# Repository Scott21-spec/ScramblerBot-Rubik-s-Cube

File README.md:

# ScramblerBot-Rubik's-Cube-For WCA Competitions
Robot capaz de resolver o desarmar cualquier cubo de rubik 3x3 con el uso servomotores, cámara e inteligencia artificial para la detección de colores, figuras o números.

Es la mejor opción para su uso en las competencias internacionales y nacionales de cubo de rubik (WCA), debido a que sólo se coloca el cubo dentro del robot sin necesidad de modificar el cubo o utilizar un cubo especial para su reconocimiento del estado actual.

Modos de uso:
  - Modo de Desordenamiento (Scrambler mode): 
En este modo, el sistema actúa como un actuador esclavo para competencias oficiales. Recibe de forma remota una secuencia de desordenamiento (algoritmo de scramble) validada por la WCA. Tras la ejecución mecánica automatizada de los movimientos, el servidor web local genera un reporte digital en formato PDF. Este documento incluye el registro exacto de la secuencia aplicada, el algoritmo de resolución correspondiente y representaciones gráficas del estado final del cubo (planos 2D y renderizado 3D). Por normativas de seguridad y confidencialidad competitiva, el acceso a este reporte es de carácter restringido, alojándose únicamente en el entorno del servidor para la validación exclusiva de los jueces o administradores del torneo.

  - Modo de Autogeneración y Entrenamiento (Auto-Scramble & Practice Mode):
Concebida como una herramienta de entrenamiento para competidores (speedcubers), esta modalidad permite al microcontrolador generar de manera autónoma una secuencia aleatoria de desordenamiento que cumple estrictamente con los estándares y métricas de la WCA. Una vez que el robot aplica mecánicamente la secuencia generada, el sistema emite un reporte digital homólogo al de la Modalidad 1. A diferencia del modo oficial, este documento es de acceso público y descargable a través de la interfaz web, permitiendo al usuario analizar el estado del cubo, la secuencia aplicada y la solución teórica propuesta para fines de estudio y práctica.

  - Resolución Optimizada (Solve Mode):
Orientada al análisis algorítmico, esta función permite evaluar el estado físico actual de un cubo ingresado por el usuario utilizando el sistema de visión artificial integrado. A partir del mapeo de las caras, el procesador calcula la ruta de resolución más corta (optimizando la cantidad de movimientos requeridos) y procede a su ejecución mecánica. Finalmente, el sistema documenta el proceso generando un reporte descargable que detalla el estado inicial detectado, la cinemática de los movimientos aplicados y la solución óptima ejecutada.

Proyecto de la materia 'Proyecto 3' del 8vo semestre de la carrera Mecatrónica - Facultad de Ingeniería - Universidad Nacional de Asunción - San Lorenzo - Paraguay.

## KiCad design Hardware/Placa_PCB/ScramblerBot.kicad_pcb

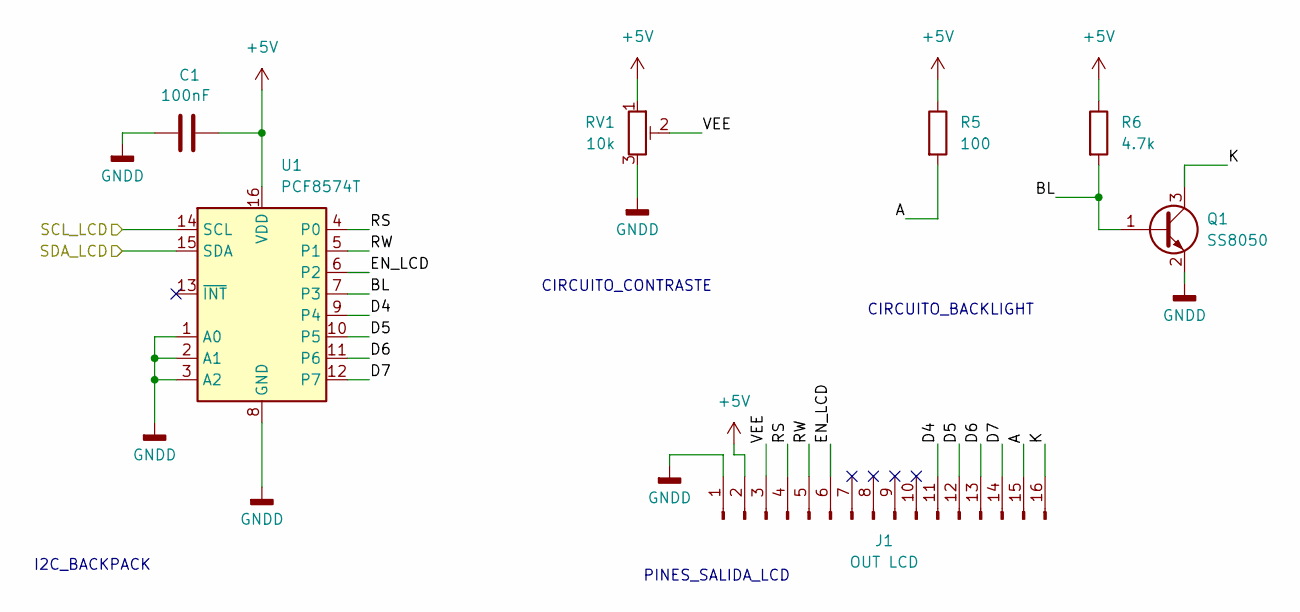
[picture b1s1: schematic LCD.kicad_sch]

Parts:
C1: 100nF; C_0805_2012Metric_Pad1.18x1.45mm_HandSolder
J1: OUT LCD; PinSocket_1x16_P2.54mm_Vertical
Q1: SS8050; SOT-23
R5: 100; R_0805_2012Metric_Pad1.20x1.40mm_HandSolder
R6: 4.7k; R_0805_2012Metric_Pad1.20x1.40mm_HandSolder
RV1: 10k; Potentiometer_Bourns_3314G_Vertical
U1: PCF8574T; SOIC-16W_7.5x10.3mm_P1.27mm

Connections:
+5V: C1.1, J1.2, R5.1, R6.1, RV1.1, U1.16 (VDD); also elsewhere on the board
/Level Shifter LCD/SCL_LCD: U1.14 (SCL); also elsewhere on the board
/Level Shifter LCD/SDA_LCD: U1.15 (SDA); also elsewhere on the board
/Pantalla_LCD/A: J1.15, R5.2
/Pantalla_LCD/BL: Q1.1 (B), R6.2, U1.7 (P3)
/Pantalla_LCD/D4: J1.11, U1.9 (P4)
/Pantalla_LCD/D5: J1.12, U1.10 (P5)
/Pantalla_LCD/D6: J1.13, U1.11 (P6)
/Pantalla_LCD/D7: J1.14, U1.12 (P7)
/Pantalla_LCD/EN_LCD: J1.6, U1.6 (P2)
/Pantalla_LCD/K: J1.16, Q1.3 (C)
/Pantalla_LCD/RS: J1.4, U1.4 (P0)
/Pantalla_LCD/RW: J1.5, U1.5 (P1)
/Pantalla_LCD/VEE: J1.3, RV1.2
GNDD: C1.2, J1.1, Q1.2 (E), RV1.3, U1.1 (A0), U1.2 (A1), U1.3 (A2), U1.8 (GND); also elsewhere on the board

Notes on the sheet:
CIRCUITO_BACKLIGHT
I2C_BACKPACK
CIRCUITO_CONTRASTE
PINES_SALIDA_LCD

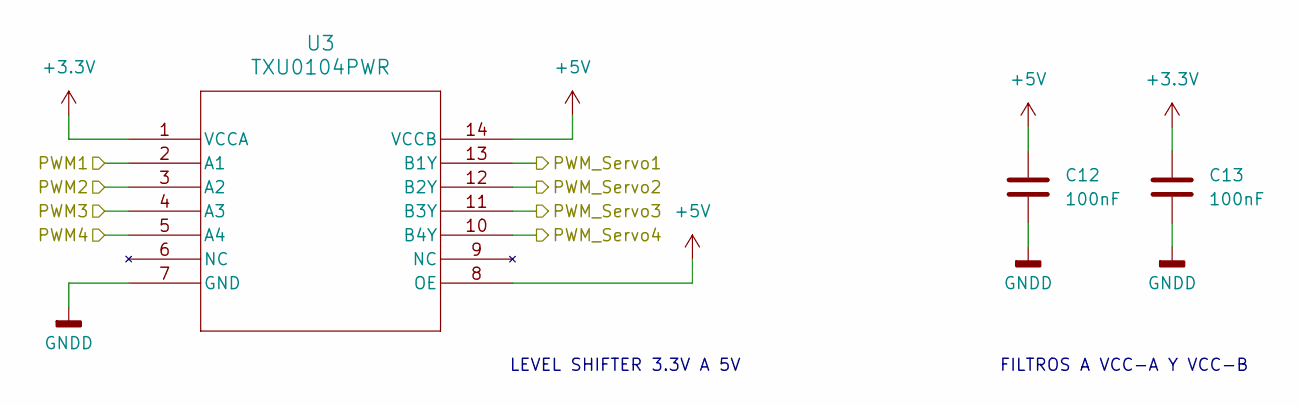
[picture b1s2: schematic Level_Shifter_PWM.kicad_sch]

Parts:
C12, C13: 100nF; C_0805_2012Metric_Pad1.18x1.45mm_HandSolder
U3: TXU0104PWR; TSSOP-14_4.4x5mm_P0.65mm

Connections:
+3.3V: C13.1, U3.1 (VCCA); also elsewhere on the board
+5V: C12.1, U3.8 (OE), U3.14 (VCCB); also elsewhere on the board
/Level Shifter PWM/PWM1: U3.2 (A1); also elsewhere on the board
/Level Shifter PWM/PWM2: U3.3 (A2); also elsewhere on the board
/Level Shifter PWM/PWM3: U3.4 (A3); also elsewhere on the board
/Level Shifter PWM/PWM4: U3.5 (A4); also elsewhere on the board
/Level Shifter PWM/PWM_Servo1: U3.13 (B1Y); also elsewhere on the board
/Level Shifter PWM/PWM_Servo2: U3.12 (B2Y); also elsewhere on the board
/Level Shifter PWM/PWM_Servo3: U3.11 (B3Y); also elsewhere on the board
/Level Shifter PWM/PWM_Servo4: U3.10 (B4Y); also elsewhere on the board
GNDD: C12.2, C13.2, U3.7 (GND); also elsewhere on the board

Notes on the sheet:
FILTROS A VCC-A Y VCC-B
LEVEL SHIFTER 3.3V A 5V

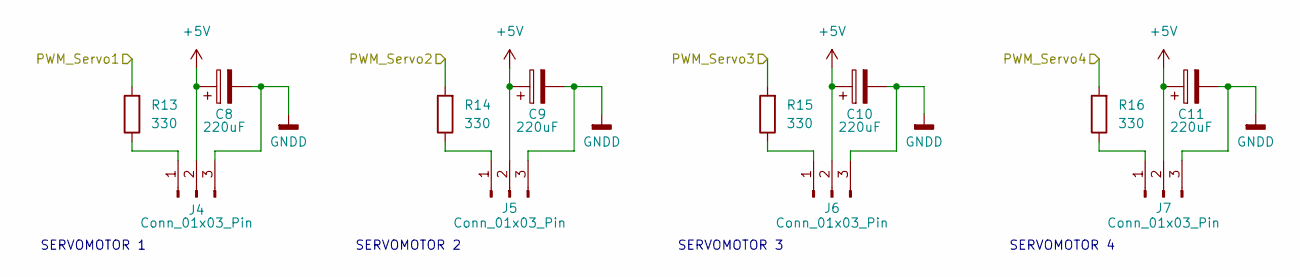
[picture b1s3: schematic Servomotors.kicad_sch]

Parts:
C8, C9, C10, C11: 220uF; CP_Elec_8x6.2
J4, J5, J6, J7: Conn_01x03_Pin; PinHeader_1x03_P2.54mm_Vertical
R13, R14, R15, R16: 330; R_0805_2012Metric_Pad1.20x1.40mm_HandSolder

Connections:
+5V: C8.1, C9.1, C10.1, C11.1, J4.2, J5.2, J6.2, J7.2; also elsewhere on the board
/Level Shifter PWM/PWM_Servo1: R13.2; also elsewhere on the board
/Level Shifter PWM/PWM_Servo2: R14.2; also elsewhere on the board
/Level Shifter PWM/PWM_Servo3: R15.2; also elsewhere on the board
/Level Shifter PWM/PWM_Servo4: R16.2; also elsewhere on the board
GNDD: C8.2, C9.2, C10.2, C11.2, J4.3, J5.3, J6.3, J7.3; also elsewhere on the board
unnamed: J4.1, R13.1
unnamed: J5.1, R14.1
unnamed: J6.1, R15.1
unnamed: J7.1, R16.1

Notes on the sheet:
SERVOMOTOR 2
SERVOMOTOR 1
SERVOMOTOR 3
SERVOMOTOR 4

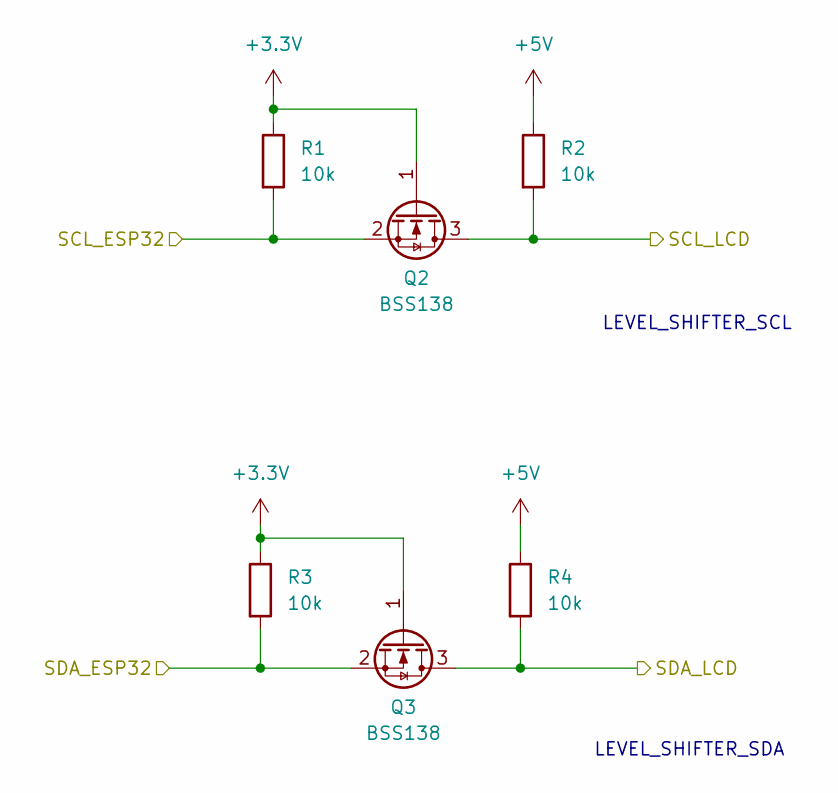
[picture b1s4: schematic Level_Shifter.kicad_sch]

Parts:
Q2, Q3: BSS138; SOT-23
R1, R2, R3, R4: 10k; R_0805_2012Metric_Pad1.20x1.40mm_HandSolder

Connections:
+3.3V: Q2.1 (G), Q3.1 (G), R1.1, R3.1; also elsewhere on the board
+5V: R2.1, R4.1; also elsewhere on the board
/Level Shifter LCD/SCL_ESP32: Q2.2 (S), R1.2; also elsewhere on the board
/Level Shifter LCD/SCL_LCD: Q2.3 (D), R2.2; also elsewhere on the board
/Level Shifter LCD/SDA_ESP32: Q3.2 (S), R3.2; also elsewhere on the board
/Level Shifter LCD/SDA_LCD: Q3.3 (D), R4.2; also elsewhere on the board

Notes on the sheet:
LEVEL_SHIFTER_SDA
LEVEL_SHIFTER_SCL

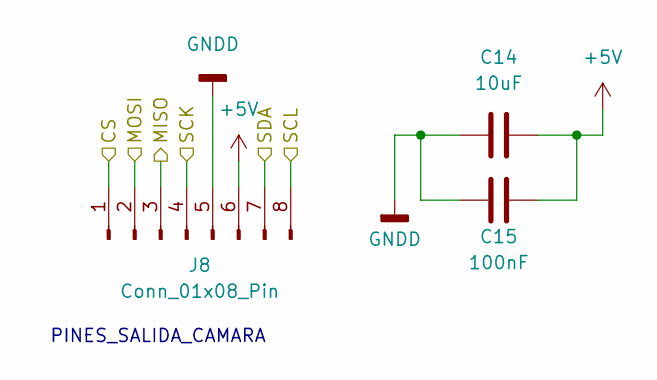
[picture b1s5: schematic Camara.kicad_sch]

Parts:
C14: 10uF; C_0805_2012Metric_Pad1.18x1.45mm_HandSolder
C15: 100nF; C_0805_2012Metric_Pad1.18x1.45mm_HandSolder
J8: Conn_01x08_Pin; PinHeader_1x08_P2.54mm_Vertical

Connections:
+5V: C14.2, C15.1, J8.6; also elsewhere on the board
/Camara/CS: J8.1; also elsewhere on the board
/Camara/MISO: J8.3; also elsewhere on the board
/Camara/MOSI: J8.2; also elsewhere on the board
/Camara/SCK: J8.4; also elsewhere on the board
/Camara/SCL: J8.8; also elsewhere on the board
/Camara/SDA: J8.7; also elsewhere on the board
GNDD: C14.1, C15.2, J8.5; also elsewhere on the board

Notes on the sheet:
PINES_SALIDA_CAMARA

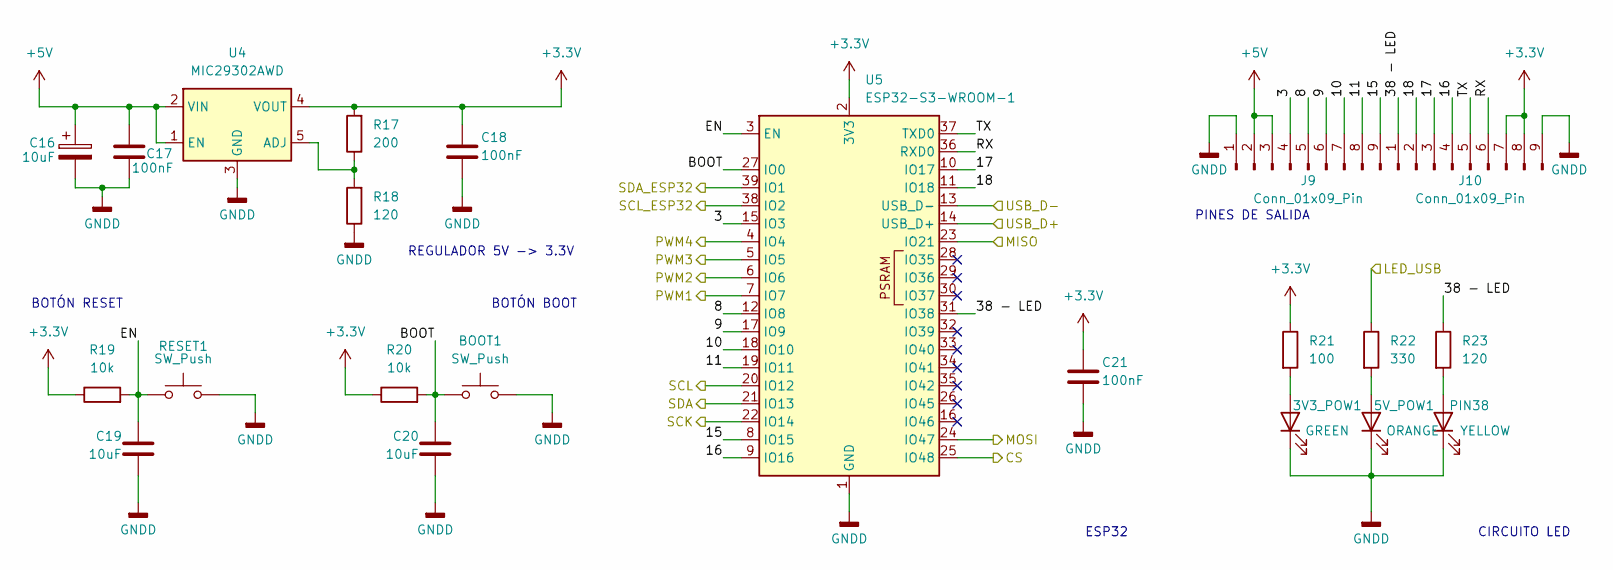
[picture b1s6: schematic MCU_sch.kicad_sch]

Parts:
3V3_POW1: GREEN; LED_0805_2012Metric_Pad1.15x1.40mm_HandSolder
5V_POW1: ORANGE; LED_0805_2012Metric_Pad1.15x1.40mm_HandSolder
BOOT1: SW_Push; SW_Push_1P1T_NO_E-Switch_TL3301NxxxxxG
C16: 10uF; CP_Elec_4x5.4
C17, C18, C21: 100nF; C_0805_2012Metric_Pad1.18x1.45mm_HandSolder
C19, C20: 10uF; C_0805_2012Metric_Pad1.18x1.45mm_HandSolder
J9, J10: Conn_01x09_Pin; PinSocket_1x09_P2.54mm_Vertical
PIN38: YELLOW; LED_0805_2012Metric_Pad1.15x1.40mm_HandSolder
R17: 200; R_0805_2012Metric_Pad1.20x1.40mm_HandSolder
R18, R23: 120; R_0805_2012Metric_Pad1.20x1.40mm_HandSolder
R19, R20: 10k; R_0805_2012Metric_Pad1.20x1.40mm_HandSolder
R21: 100; R_0805_2012Metric_Pad1.20x1.40mm_HandSolder
R22: 330; R_0805_2012Metric_Pad1.20x1.40mm_HandSolder
RESET1: SW_Push; SW_Push_1P1T_NO_E-Switch_TL3301NxxxxxG
U4: MIC29302AWD; TO-252-5_TabPin3
U5: ESP32-S3-WROOM-1

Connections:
+3.3V: C18.1, C21.1, J10.7, J10.8, R17.2, R19.1, R20.1, R21.1, U4.4 (VOUT), U5.2 (3V3); also elsewhere on the board
+5V: C16.1, C17.1, J9.2, J9.3, U4.1 (EN), U4.2 (VIN); also elsewhere on the board
/Camara/CS: U5.25 (IO48); also elsewhere on the board
/Camara/MISO: U5.23 (IO21); also elsewhere on the board
/Camara/MOSI: U5.24 (IO47); also elsewhere on the board
/Camara/SCK: U5.22 (IO14); also elsewhere on the board
/Camara/SCL: U5.20 (IO12); also elsewhere on the board
/Camara/SDA: U5.21 (IO13); also elsewhere on the board
/Level Shifter LCD/SCL_ESP32: U5.38 (IO2); also elsewhere on the board
/Level Shifter LCD/SDA_ESP32: U5.39 (IO1); also elsewhere on the board
/Level Shifter PWM/PWM1: U5.7 (IO7); also elsewhere on the board
/Level Shifter PWM/PWM2: U5.6 (IO6); also elsewhere on the board
/Level Shifter PWM/PWM3: U5.5 (IO5); also elsewhere on the board
/Level Shifter PWM/PWM4: U5.4 (IO4); also elsewhere on the board
/MCU/3: J9.4, U5.15 (IO3)
/MCU/8: J9.5, U5.12 (IO8)
/MCU/9: J9.6, U5.17 (IO9)
/MCU/10: J9.7, U5.18 (IO10)
/MCU/11: J9.8, U5.19 (IO11)
/MCU/15: J9.9, U5.8 (IO15)
/MCU/16: J10.4, U5.9 (IO16)
/MCU/17: J10.3, U5.10 (IO17)
/MCU/18: J10.2, U5.11 (IO18)
/MCU/38 - LED: J10.1, R23.1, U5.31 (IO38)
/MCU/BOOT: BOOT1.1, C20.1, R20.2, U5.27 (IO0)
/MCU/EN: C19.1, R19.2, RESET1.1, U5.3 (EN)
/MCU/LED_USB: R22.1; also elsewhere on the board
/MCU/RX: J10.6, U5.36 (RXD0)
/MCU/TX: J10.5, U5.37 (TXD0)
/MCU/USB_D+: U5.14 (USB_D+); also elsewhere on the board
/MCU/USB_D-: U5.13 (USB_D-); also elsewhere on the board
GNDD: 3V3_POW1.1 (K), 5V_POW1.1 (K), BOOT1.2, C16.2, C17.2, C18.2, C19.2, C20.2, C21.2, J9.1, J10.9, PIN38.1 (K), R18.1, RESET1.2, U4.3 (GND), U5.1 (GND), U5.40 (GND), U5.41 (GND); also elsewhere on the board
unnamed: 3V3_POW1.2 (A), R21.2
unnamed: 5V_POW1.2 (A), R22.2
unnamed: PIN38.2 (A), R23.2
unnamed: R17.1, R18.2, U4.5 (ADJ)

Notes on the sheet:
REGULADOR 5V -> 3.3V
CIRCUITO LED
BOTÓN BOOT
PINES DE SALIDA
BOTÓN RESET
ESP32

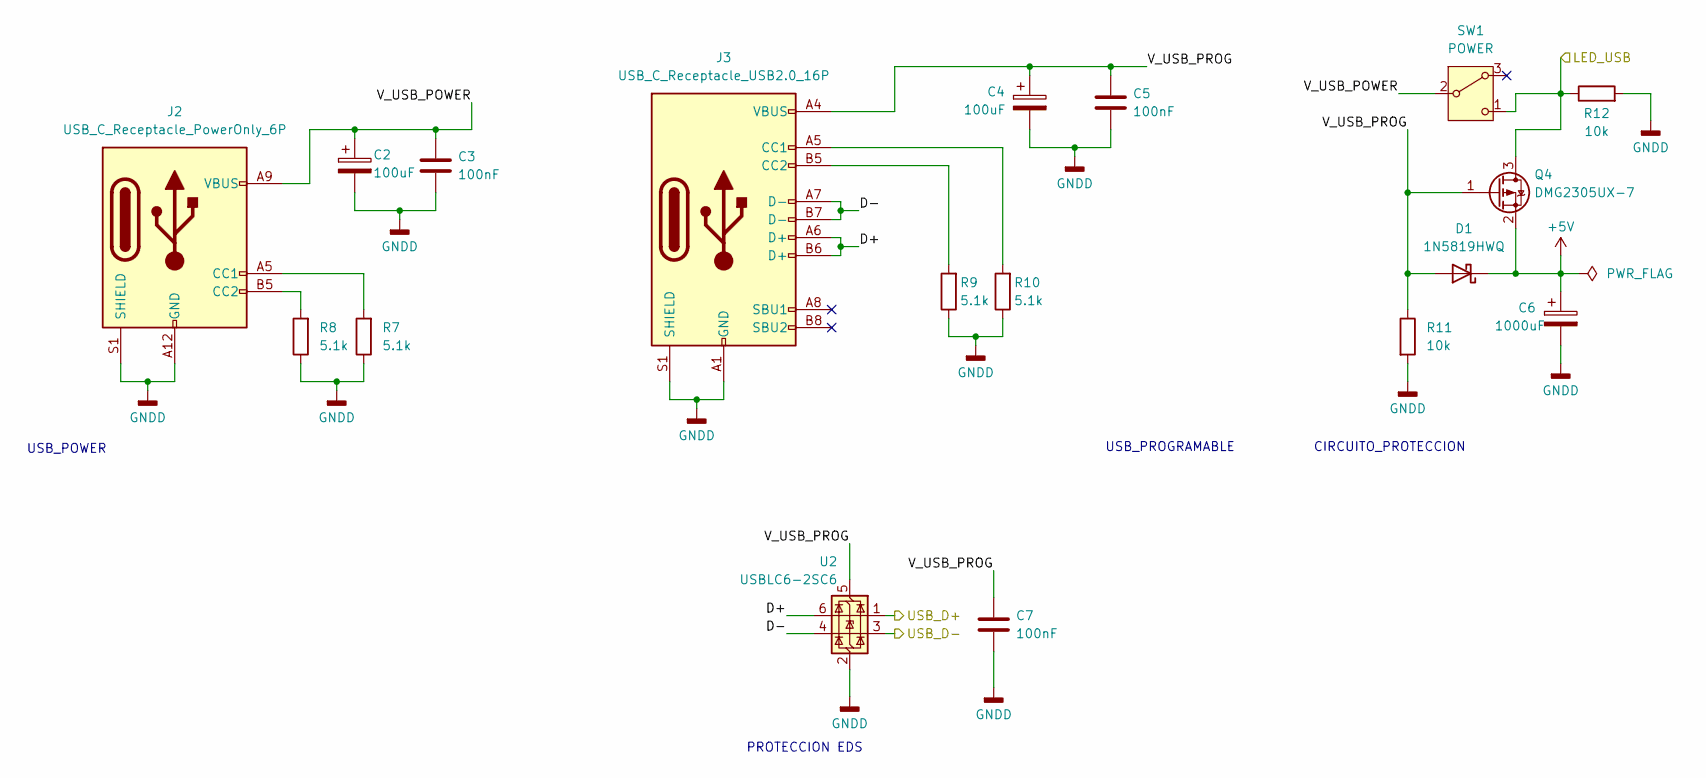
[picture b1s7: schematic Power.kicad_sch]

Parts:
C2, C4: 100uF; CP_Elec_6.3x5.8
C3, C5, C7: 100nF; C_0805_2012Metric_Pad1.18x1.45mm_HandSolder
C6: 1000uF; CP_Elec_10x10.5
D1: 1N5819HWQ; D_SOD-123
J2: USB_C_Receptacle_PowerOnly_6P; USB_C_Receptacle_GCT_USB4125-xx-x-0190_6P_TopMnt_Horizontal
J3: USB_C_Receptacle_USB2.0_16P; USB_C_Receptacle_HRO_TYPE-C-31-M-12
Q4: DMG2305UX-7; SOT-23
R7, R8, R9, R10: 5.1k; R_0805_2012Metric_Pad1.20x1.40mm_HandSolder
R11, R12: 10k; R_0805_2012Metric_Pad1.20x1.40mm_HandSolder
SW1: POWER; SW_100SP1T_12P7X6P86_EWI
U2: USBLC6-2SC6; SOT-23-6

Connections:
+5V: C6.1, D1.1 (K), Q4.2 (S); also elsewhere on the board
/MCU/LED_USB: Q4.3 (D), R12.1, SW1.1 (C); also elsewhere on the board
/MCU/USB_D+: U2.1 (I/O1); also elsewhere on the board
/MCU/USB_D-: U2.3 (I/O2); also elsewhere on the board
/Power__USB_C/D+: J3.A6 (D+), J3.B6 (D+), U2.6 (I/O1)
/Power__USB_C/D-: J3.A7 (D-), J3.B7 (D-), U2.4 (I/O2)
/Power__USB_C/V_USB_POWER: C2.1, C3.1, J2.A9 (VBUS), J2.B9 (VBUS), SW1.2 (B)
/Power__USB_C/V_USB_PROG: C4.1, C5.1, C7.1, D1.2 (A), J3.A4 (VBUS), J3.A9 (VBUS), J3.B4 (VBUS), J3.B9 (VBUS), Q4.1 (G), R11.1, U2.5 (VBUS)
GNDD: C2.2, C3.2, C4.2, C5.2, C6.2, C7.2, J2.A12 (GND), J2.B12 (GND), J2.S1 (SHIELD), J3.A1 (GND), J3.A12 (GND), J3.B1 (GND), J3.B12 (GND), J3.S1 (SHIELD), R7.1, R8.1, R9.1, R10.1, R11.2, R12.2, U2.2 (GND); also elsewhere on the board
unnamed: J2.A5 (CC1), R7.2
unnamed: J2.B5 (CC2), R8.2
unnamed: J3.A5 (CC1), R10.2
unnamed: J3.B5 (CC2), R9.2

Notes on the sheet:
CIRCUITO_PROTECCION
PROTECCION EDS
USB_POWER
USB_PROGRAMABLE

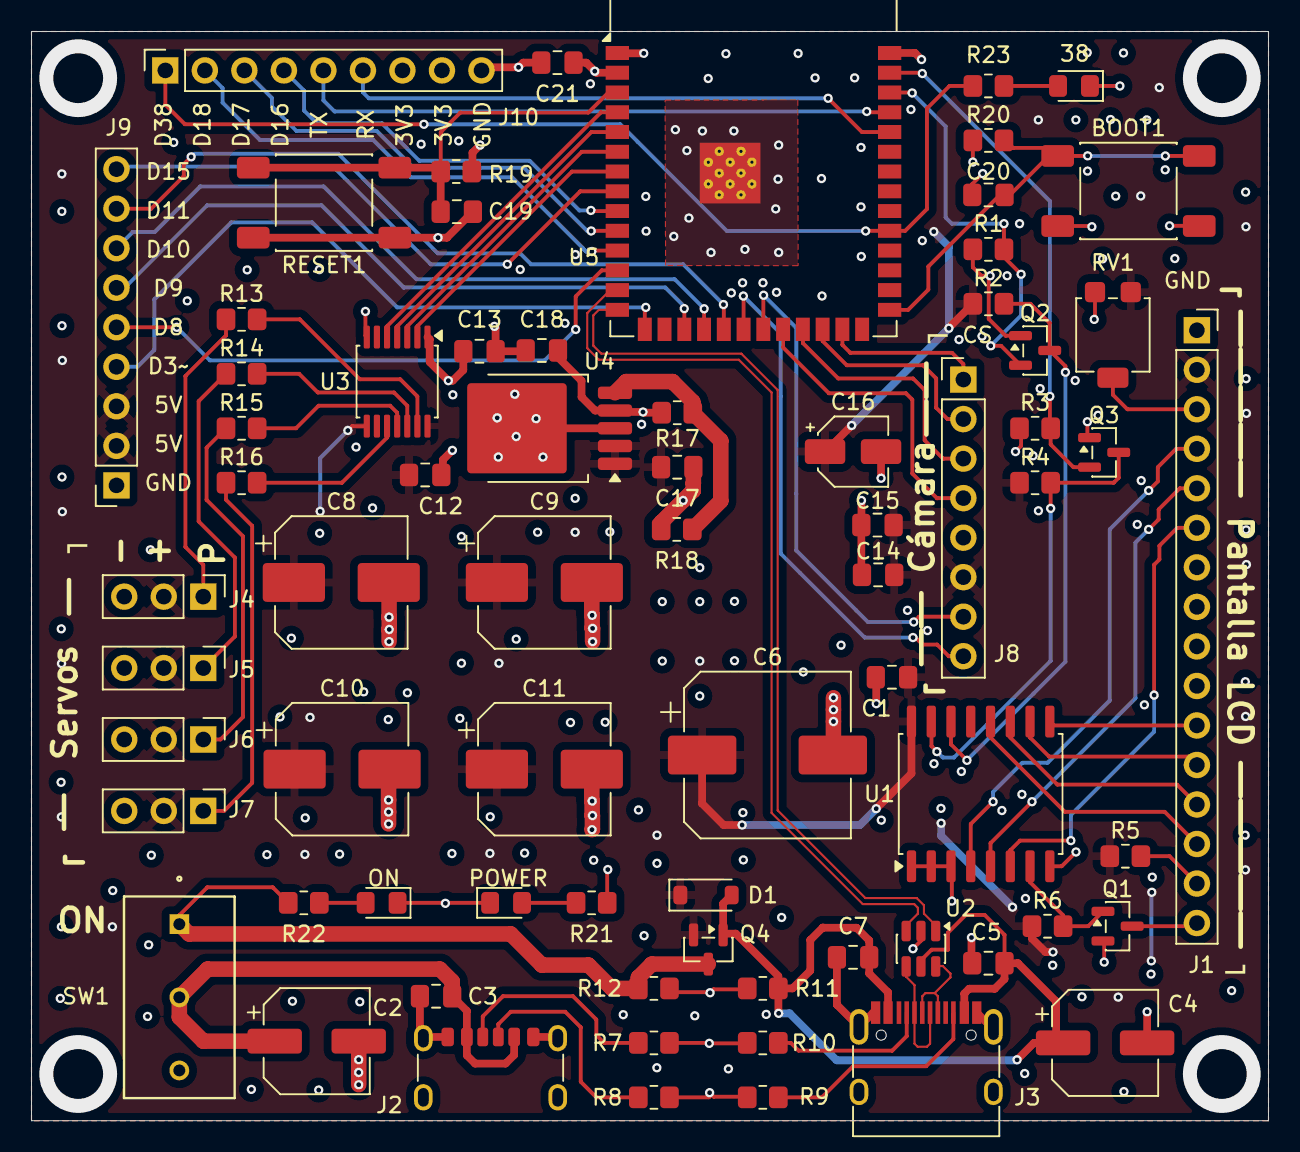
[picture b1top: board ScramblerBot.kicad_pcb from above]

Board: 4 copper layers, 79.5 x 70.0 mm, 71 parts (0 on the bottom side), 65 nets.

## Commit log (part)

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2026-02-25 Create Lista_Actuadores_Periféricos
2026-02-25 Create Schematic
2026-02-25 Create Actividades_a_Realizar
2026-03-03 Update and rename Lista_Actuadores_Periféricos.xls to Lista_Actuadores_Periféricos
2026-03-03 Update Lista_Actuadores_Periféricos
2026-03-09 Create Objetivos
2026-03-09 Agregando carpeta Placa_PCB dentro del Hardware y los archivos Kicad
2026-03-09 Create Codigo
2026-03-09 Agregando excel de Lista de Componentes dentro de la carpeta Hardware
2026-03-10 Cambiando descripcion de la camara
2026-03-10 Rename Lista_Actuadores_Periféricos to Lista_Actuadores_Periféricos.txt
2026-03-10 Rename Actividades_a_Realizar to Actividades_a_Realizar.txt
2026-03-10 Rename Objetivos to Objetivos.txt
2026-03-11 Agregando Level Shifter al PWM del Servo
2026-03-11 Agregando carpeta Assets para los simbolos que no existen
2026-03-13 Agregando MCU al esquematico
2026-03-15 Esquematico Final
2026-03-16 Agregando huella del capacitor de 10uF y comenzando con el PCB (USB + Alimentacion)
2026-03-18 Acomodando los componentes en el PCB y cambiendo las conexiones con el ESP32
2026-03-19 Terminando el enrutado de los +5V y comenzando las pistas de 3.3V
2026-03-21 Actualizacion de PCB con rellenos ordenados, solo falta colocar las vias
2026-03-21 PCB Final 1
2026-03-21 Acomodando capacitor electrolitico de entrada
2026-03-28 Cambiando algunos errores de DMF y creando Gerbers
2026-03-30 Agregando Lista_Componentes.xls e Informe.pdf dentro de la carpeta Informe
2026-04-23 Gerber Final
2026-05-28 Creamos el primer codigo de prueba 'hello_world' dentro de Software
2026-06-01 Creando programa simulacion
